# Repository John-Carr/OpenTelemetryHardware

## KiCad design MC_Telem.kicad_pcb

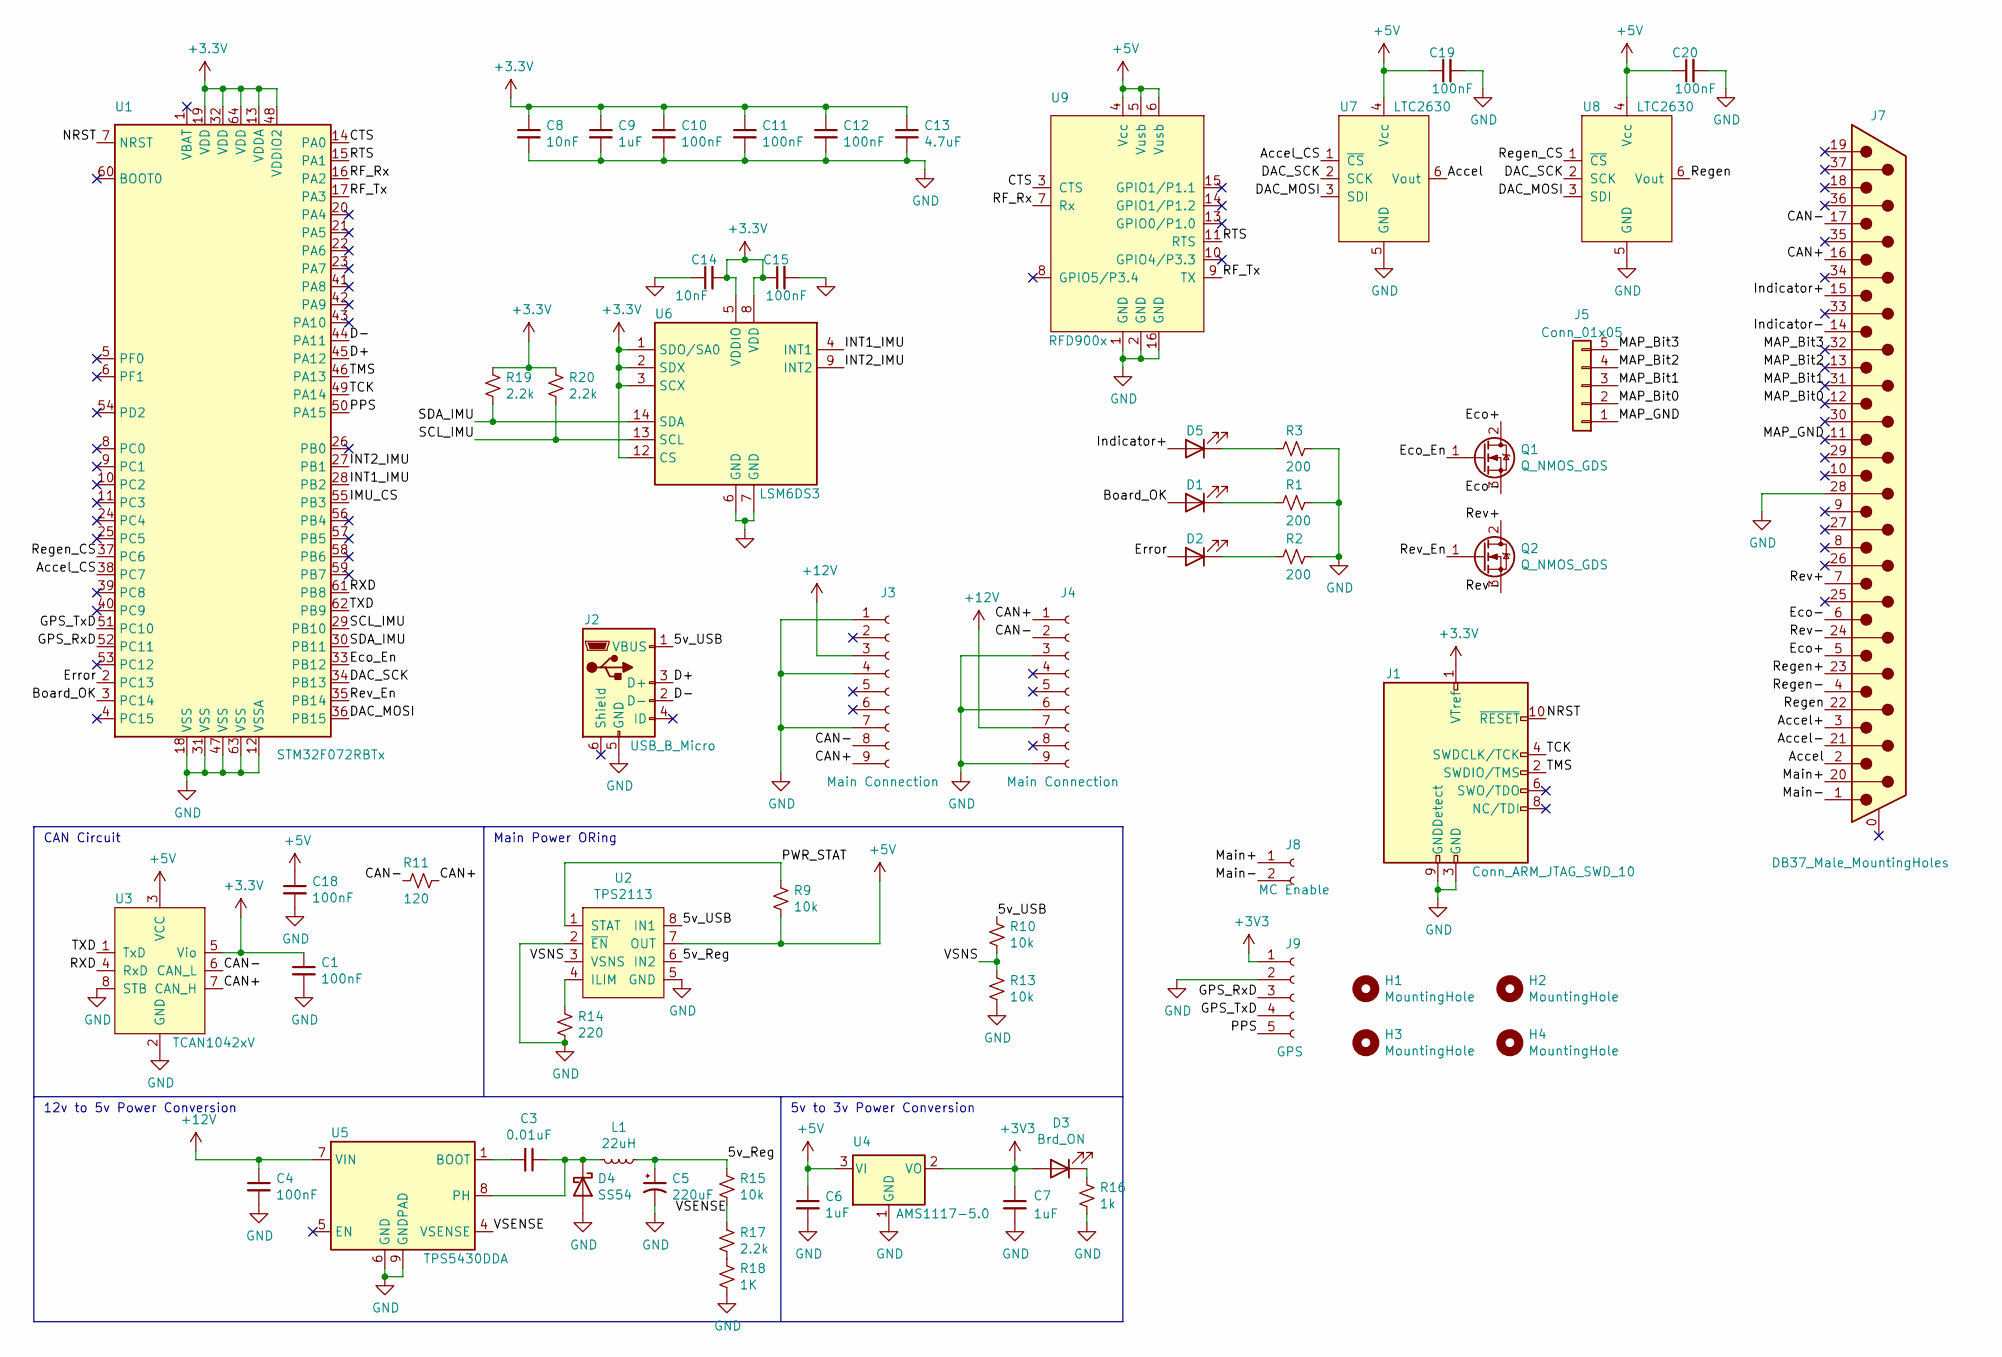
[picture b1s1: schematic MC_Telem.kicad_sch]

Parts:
C1, C4, C10, C11, C12, C15, C18, C19, C20: 100nF; C_0402_1005Metric; LCSC# C307331
C3: 0.01uF; C_0402_1005Metric; LCSC# C15195
C5: 220uF; CP_Elec_8x5.4; LCSC# C3345
C6, C7, C9: 1uF; C_0402_1005Metric; LCSC# C52923
C8, C14: 10nF; C_0402_1005Metric; LCSC# C15195
C13: 4.7uF; C_0402_1005Metric; LCSC# C23733
D1: Board OK; LED_0805_2012Metric; LCSC# C2297
D2: Error; LED_0603_1608Metric; LCSC# C2286
D3: Brd_ON; LED_0805_2012Metric; LCSC# C2297
D4: SS54; D_SMA; LCSC# C22452
D5: Board OK; LED_0805_2012Metric; LCSC# C34499
H1, H2, H3, H4: MountingHole; MountingHole_3.2mm_M3
J1: Conn_ARM_JTAG_SWD_10; PinHeader_2x05_P1.27mm_Vertical_SMD
J2: USB_B_Micro; USB_Micro-B_Molex_47346-0001
J3, J4: Main Connection; Molex_Micro-Fit_3.0_43650-0900_1x09_P3.00mm_Horizontal
J5: Conn_01x05; SolderWire-0.75sqmm_1x05_P4.8mm_D1.25mm_OD2.3mm
J7: DB37_Male_MountingHoles; DSUB-37_Male_Horizontal_P2.77x2.84mm_EdgePinOffset7.70mm_Ho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
J8: MC Enable; Molex_Micro-Fit_3.0_43650-0200_1x02_P3.00mm_Horizontal
J9: GPS; PinSocket_1x05_P2.54mm_Vertical
L1: 22uH; L_Panasonic_YFP; LCSC# C38117
Q1, Q2: Q_NMOS_GDS; SOT-23; LCSC# C20917
R1, R2, R3: 200; R_0603_1608Metric; LCSC# C8218
R9, R10, R13, R15: 10k; R_0603_1608Metric; LCSC# C25804
R11: 120; R_1206_3216Metric_Pad1.30x1.75mm_HandSolder
R14: 220; R_0603_1608Metric; LCSC# C22962
R16: 1k; R_0603_1608Metric; LCSC# C21190
R17, R19, R20: 2.2k; R_0603_1608Metric; LCSC# C4190
R18: 1K; R_0603_1608Metric; LCSC# C21190
U1: STM32F072RBTx; LQFP-64_10x10mm_P0.5mm
U2: TPS2113; TSSOP-8_4.4x3mm_P0.65mm
U3: TCAN1042xV; SOIC-8
U4: AMS1117-5.0; SOT-223-3_TabPin2; LCSC# C6186
U5: TPS5430DDA; TI_SO-PowerPAD-8_ThermalVias; LCSC# C9864
U6: LSM6DS3; LGA-14_3x2.5mm_P0.5mm_LayoutBorder3x4y; LCSC# C784817
U7, U8: LTC2630; SOT-363_SC-70-6_Handsoldering
U9: RFD900x

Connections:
+5V: C6.1, C18.1, C19.1, C20.1, R9.2, U2.7 (OUT), U3.3 (VCC), U4.3 (VI), U7.4 (Vcc), U8.4 (Vcc), U9.4 (Vcc), U9.5 (Vusb), U9.6 (Vusb)
+12V: C4.1, J3.3, J4.7, U5.7 (VIN)
/5v_Reg: C5.1, L1.1, R15.1, U2.6 (IN2)
/5v_USB: J2.1 (VBUS), R10.1, U2.8 (IN1)
/Accel: J7.2, U7.6 (Vout)
/Accel+: J7.3
/Accel-: J7.21
/Accel_CS: U1.38 (PC7), U7.1 (~CS)
/Board_OK: D1.2 (A), U1.3 (PC14)
/CAN+: J3.9, J4.1, J7.16, R11.2, U3.7 (CAN_H)
/CAN-: J3.8, J4.2, J7.17, R11.1, U3.6 (CAN_L)
/CTS: U1.14 (PA0), U9.3 (CTS)
/D+: J2.3 (D+), U1.45 (PA12)
/D-: J2.2 (D-), U1.44 (PA11)
/DAC_MOSI: U1.36 (PB15), U7.3 (SDI), U8.3 (SDI)
/DAC_SCK: U1.34 (PB13), U7.2 (SCK), U8.2 (SCK)
/Eco+: J7.5, Q1.2 (D)
/Eco-: J7.6, Q1.3 (S)
/Eco_En: Q1.1 (G), U1.33 (PB12)
/Error: D2.2 (A), U1.2 (PC13)
/GPS_RxD: J9.3, U1.52 (PC11)
/GPS_TxD: J9.4, U1.51 (PC10)
/IMU_CS: U1.55 (PB3)
/INT1_IMU: U1.28 (PB2), U6.4 (INT1)
/INT2_IMU: U1.27 (PB1), U6.9 (INT2)
/Indicator+: D5.2 (A), J7.15
/Indicator-: J7.14
/MAP_Bit0: J5.2, J7.12
/MAP_Bit1: J5.3, J7.31
/MAP_Bit2: J5.4, J7.13
/MAP_Bit3: J5.5, J7.32
/MAP_GND: J5.1, J7.11
/Main+: J7.20, J8.1
/Main-: J7.1, J8.2
/NRST: J1.10 (~RESET), U1.7 (NRST)
/PPS: J9.5, U1.50 (PA15)
/PWR_STAT: R9.1, U2.1 (STAT)
/RF_Rx: U1.16 (PA2), U9.7 (Rx)
/RF_Tx: U1.17 (PA3), U9.9 (TX)
/RTS: U1.15 (PA1), U9.11 (RTS)
/RXD: U1.61 (PB8), U3.4 (RxD)
/Regen: J7.22, U8.6 (Vout)
/Regen+: J7.23
/Regen-: J7.4
/Regen_CS: U1.37 (PC6), U8.1 (~CS)
/Rev+: J7.7, Q2.2 (D)
/Rev-: J7.24, Q2.3 (S)
/Rev_En: Q2.1 (G), U1.35 (PB14)
/SCL_IMU: R20.2, U1.29 (PB10), U6.13 (SCL)
/SDA_IMU: R19.2, U1.30 (PB11), U6.14 (SDA)
/TCK: J1.4 (SWDCLK/TCK), U1.49 (PA14)
/TMS: J1.2 (SWDIO/TMS), U1.46 (PA13)
/TXD: U1.62 (PB9), U3.1 (TxD)
/VSENSE: R15.2, R17.1, U5.4 (VSENSE)
/VSNS: R10.2, R13.1, U2.3 (VSNS)
GND: C1.2, C4.2, C5.2, C6.2, C7.2, C8.2, C9.2, C10.2, C11.2, C12.2, C13.2, C14.1, C15.2, C18.2, C19.2, C20.2, D4.2 (A), J1.3 (GND), J1.5 (GND), J1.9 (GNDDetect), J2.5 (GND), J3.1, J3.4, J3.7, J4.3, J4.6, J4.9, J7.28, J9.2, R1.1, R2.1, R3.1, R13.2, R14.2, R16.2, R18.2, U1.12 (VSSA), U1.18 (VSS), U1.31 (VSS), U1.47 (VSS), U1.63 (VSS), U2.2 (~EN), U2.5 (GND), U3.2 (GND), U3.8 (STB), U4.1 (GND), U5.6 (GND), U5.9 (GNDPAD), U6.6 (GND), U6.7 (GND), U7.5 (GND), U8.5 (GND), U9.1 (GND), U9.2 (GND), U9.16 (GND)
unnamed: C3.1, D4.1 (K), L1.2, U5.8 (PH)
unnamed: C3.2, U5.1 (BOOT)
unnamed: D1.1 (K), R1.2
unnamed: D2.1 (K), R2.2
unnamed: D3.1 (K), R16.1
unnamed: D5.1 (K), R3.2
unnamed: R14.1, U2.4 (ILIM)
unnamed: R17.2, R18.1

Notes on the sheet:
5v to 3v Power Conversion
CAN Circuit
Main Power ORing
12v to 5v Power Conversion

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
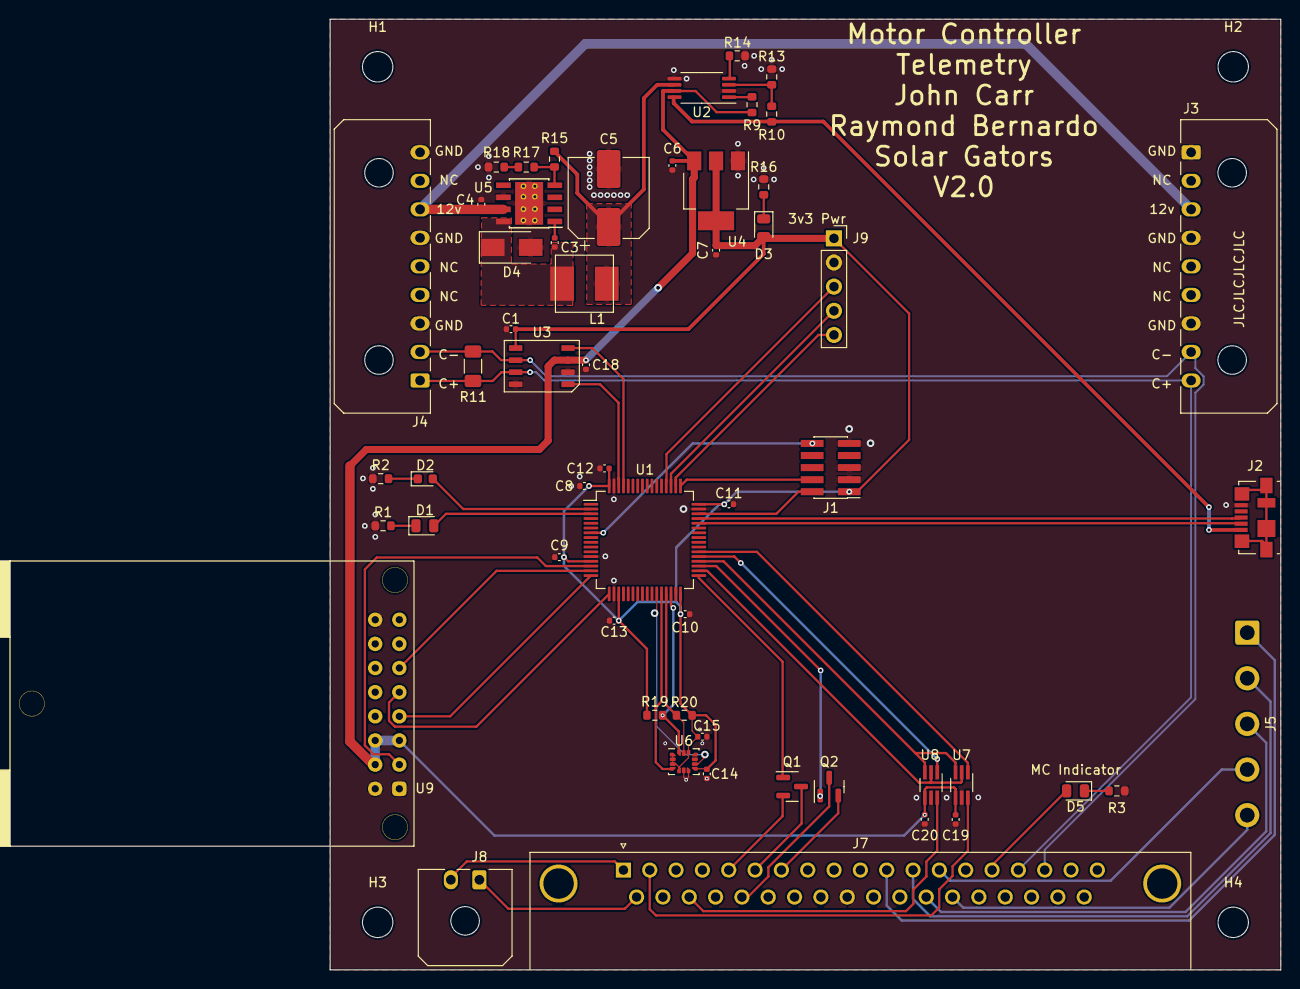
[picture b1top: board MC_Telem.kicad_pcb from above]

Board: 2 copper layers, 100.0 x 100.0 mm, 60 parts (0 on the bottom side), 59 nets.

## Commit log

2022-03-24 Version 2
2022-06-16 Adding automation
2022-06-16 Fix for automation
